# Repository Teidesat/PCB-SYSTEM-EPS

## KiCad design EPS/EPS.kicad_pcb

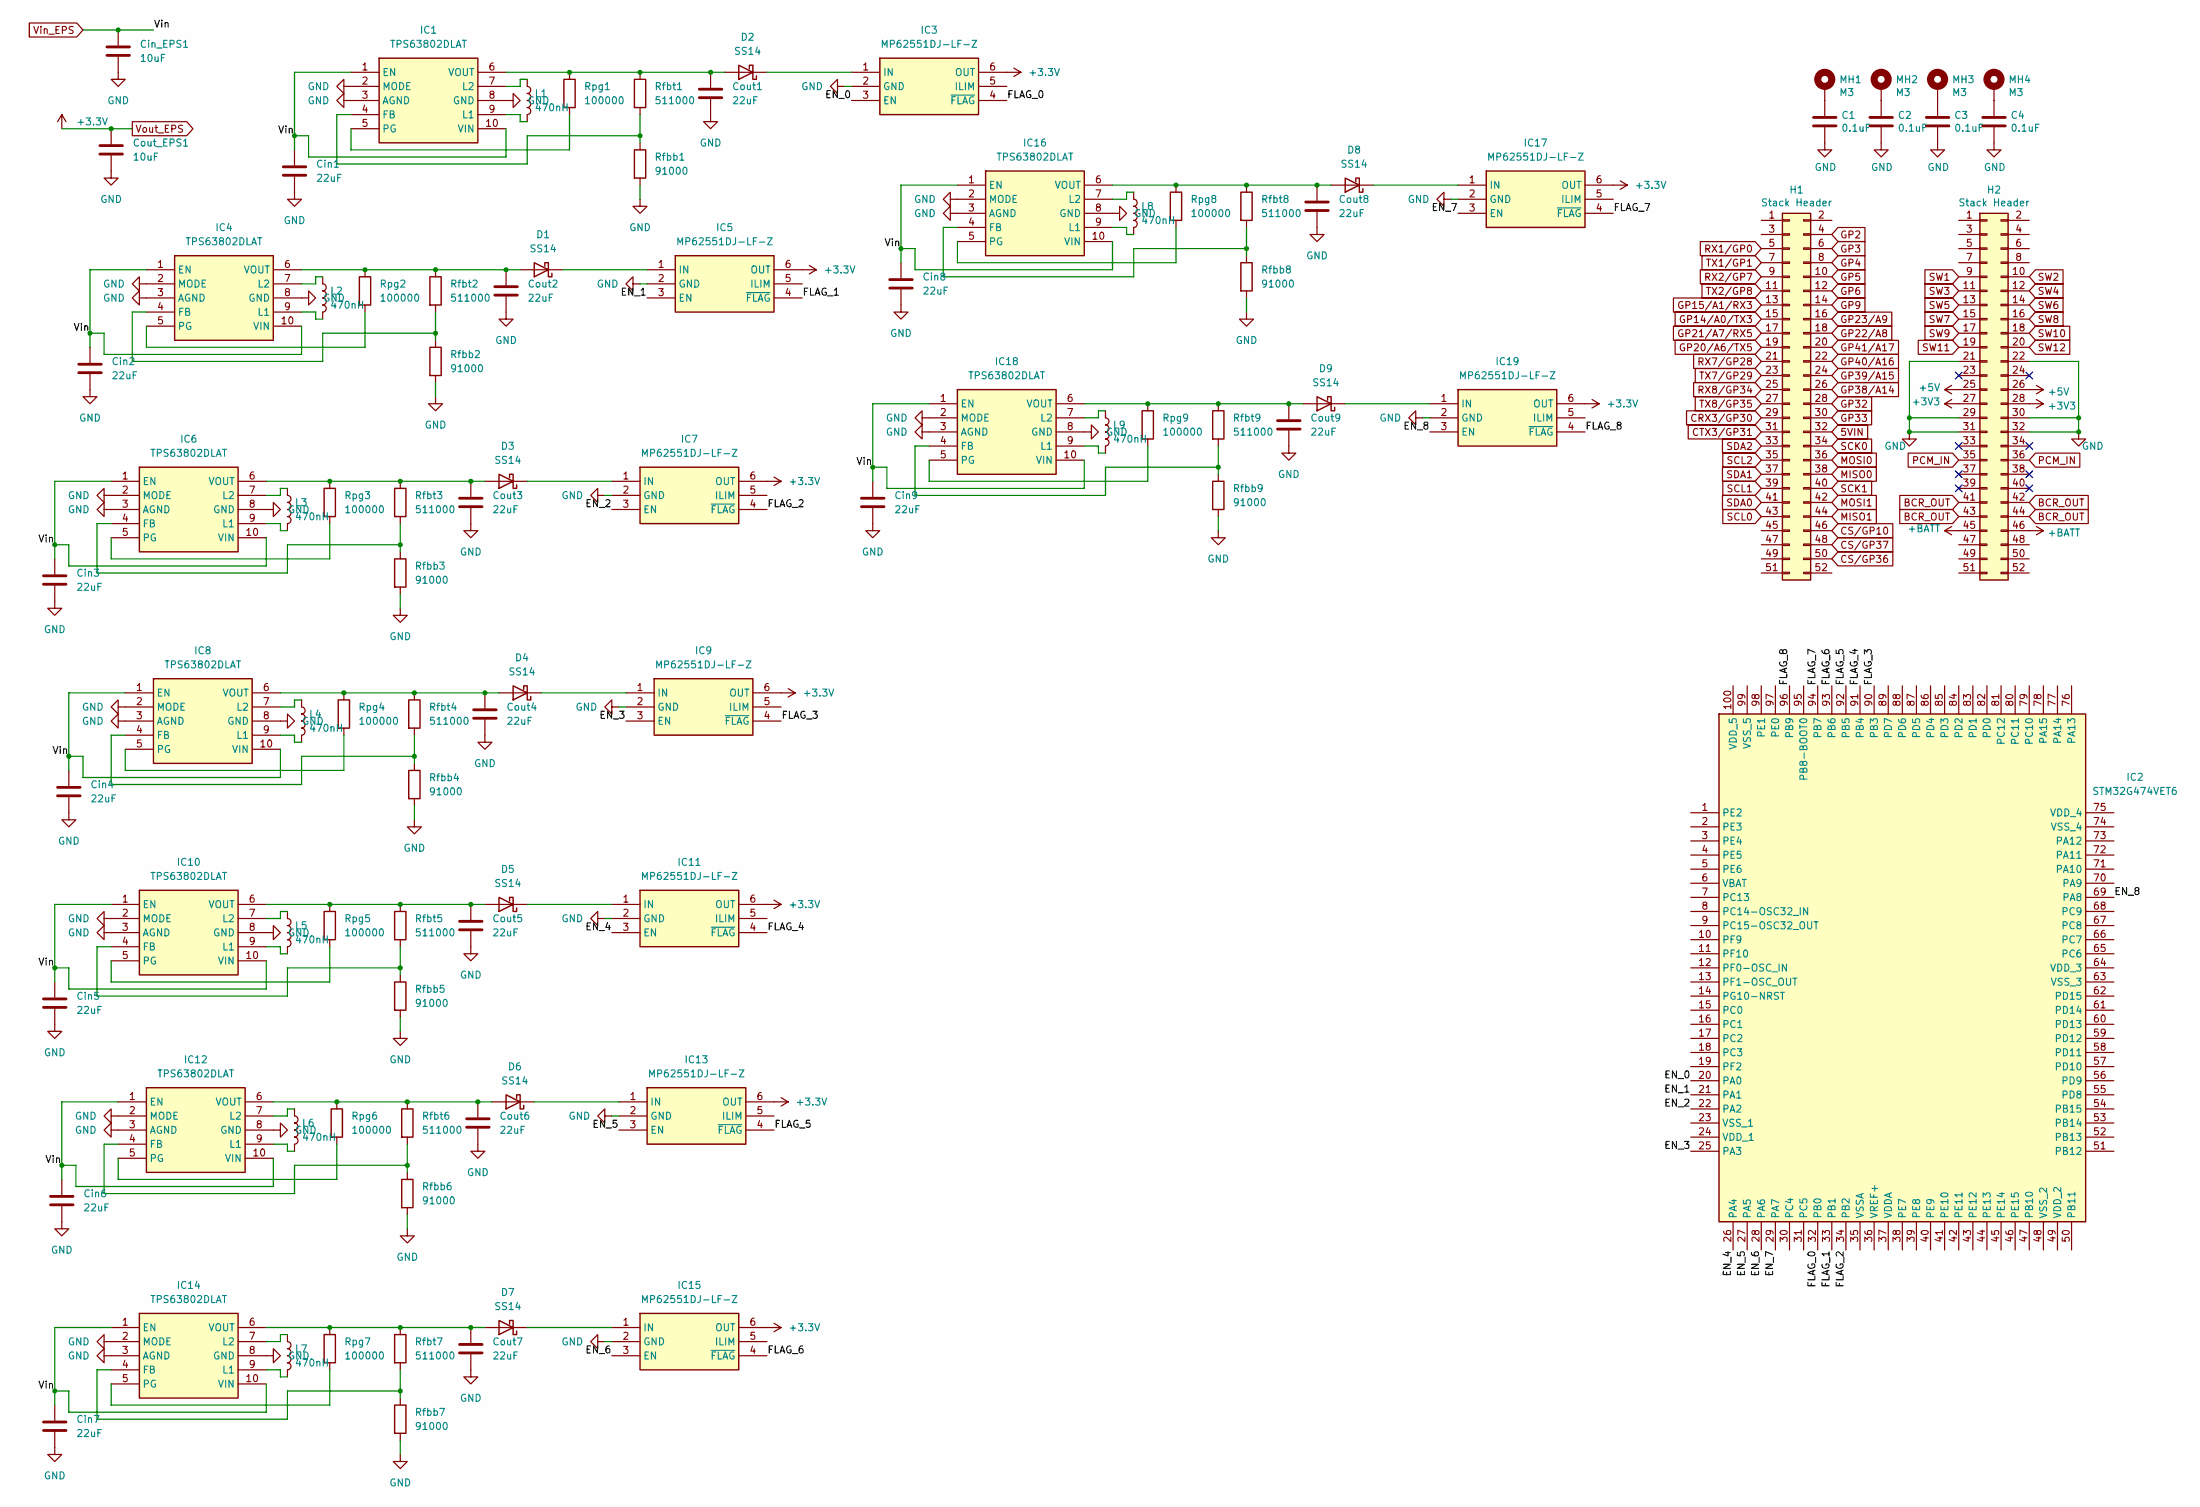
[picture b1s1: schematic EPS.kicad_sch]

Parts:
C1, C2, C3, C4: 0.1uF; C_0805_2012Metric
Cin1, Cin2, Cin3, Cin4, Cin5, Cin6, Cin7, Cin8, Cin9: 22uF; CP_Elec_6.3x4.5
Cin_EPS1: 10uF; C_0805_2012Metric
Cout1, Cout2, Cout3, Cout4, Cout5, Cout6, Cout7, Cout8, Cout9: 22uF; CP_Elec_6.3x4.5
Cout_EPS1: 10uF; C_0805_2012Metric
D1, D2, D3, D4, D5, D6, D7, D8, D9: SS14; D_SMA
H1, H2: Stack Header; PinHeader_2x26_P2.54mm_Vertical
IC1, IC4, IC6, IC8, IC10, IC12, IC14, IC16, IC18: TPS63802DLAT; Mouser Part Number 595-TPS63802DLAT
IC2: STM32G474VET6; QFP50P1600X1600X160-100N; Mouser Part Number 511-STM32G474VET6
IC3, IC5, IC7, IC9, IC11, IC13, IC15, IC17, IC19: MP62551DJ-LF-Z; SOT95P280X100-6N; Mouser Part Number 946-MP62551DJLFZ
L1, L2, L3, L4, L5, L6, L7, L8, L9: 470nH; L_1206_3216Metric_Pad1.42x1.75mm_HandSolder
MH1, MH2, MH3, MH4: M3; MountingHole_3.2mm_M3_Pad
Rfbb1, Rfbb2, Rfbb3, Rfbb4, Rfbb5, Rfbb6, Rfbb7, Rfbb8, Rfbb9: 91000; R_0603_1608Metric
Rfbt1, Rfbt2, Rfbt3, Rfbt4, Rfbt5, Rfbt6, Rfbt7, Rfbt8, Rfbt9: 511000; R_0603_1608Metric
Rpg1, Rpg2, Rpg3, Rpg4, Rpg5, Rpg6, Rpg7, Rpg8, Rpg9: 100000; R_0603_1608Metric

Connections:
5VIN: H1.32
+3V3: H2.27, H2.28
+5V: H2.25, H2.26
+BATT: H2.45, H2.46
/EN_0: IC2.20 (PA0), IC3.3 (EN)
/EN_1: IC2.21 (PA1), IC5.3 (EN)
/EN_2: IC2.22 (PA2), IC7.3 (EN)
/EN_3: IC2.25 (PA3), IC9.3 (EN)
/EN_4: IC2.26 (PA4), IC11.3 (EN)
/EN_5: IC2.27 (PA5), IC13.3 (EN)
/EN_6: IC2.28 (PA6), IC15.3 (EN)
/EN_7: IC2.29 (PA7), IC17.3 (EN)
/EN_8: IC2.69 (PA8), IC19.3 (EN)
/FLAG_0: IC2.32 (PB0), IC3.4 (~FLAG)
/FLAG_1: IC2.33 (PB1), IC5.4 (~FLAG)
/FLAG_2: IC2.34 (PB2), IC7.4 (~FLAG)
/FLAG_3: IC2.90 (PB3), IC9.4 (~FLAG)
/FLAG_4: IC2.91 (PB4), IC11.4 (~FLAG)
/FLAG_5: IC2.92 (PB5), IC13.4 (~FLAG)
/FLAG_6: IC2.93 (PB6), IC15.4 (~FLAG)
/FLAG_7: IC2.94 (PB7), IC17.4 (~FLAG)
/FLAG_8: IC2.96 (PB9), IC19.4 (~FLAG)
BCR_OUT: H2.41, H2.42, H2.43, H2.44
CRX3/GP30: H1.29
CS/GP10: H1.46
CS/GP36: H1.50
CS/GP37: H1.48
CTX3/GP31: H1.31
GND: C1.2, C2.2, C3.2, C4.2, Cin1.2, Cin2.2, Cin3.2, Cin4.2, Cin5.2, Cin6.2, Cin7.2, Cin8.2, Cin9.2, Cin_EPS1.2, Cout1.2, Cout2.2, Cout3.2, Cout4.2, Cout5.2, Cout6.2, Cout7.2, Cout8.2, Cout9.2, Cout_EPS1.2, H2.21, H2.22, H2.29, H2.30, H2.31, H2.32, IC1.2 (MODE), IC1.3 (AGND), IC1.8 (GND), IC3.2 (GND), IC4.2 (MODE), IC4.3 (AGND), IC4.8 (GND), IC5.2 (GND), IC6.2 (MODE), IC6.3 (AGND), IC6.8 (GND), IC7.2 (GND), IC8.2 (MODE), IC8.3 (AGND), IC8.8 (GND), IC9.2 (GND), IC10.2 (MODE), IC10.3 (AGND), IC10.8 (GND), IC11.2 (GND), IC12.2 (MODE), IC12.3 (AGND), IC12.8 (GND), IC13.2 (GND), IC14.2 (MODE), IC14.3 (AGND), IC14.8 (GND), IC15.2 (GND), IC16.2 (MODE), IC16.3 (AGND), IC16.8 (GND), IC17.2 (GND), IC18.2 (MODE), IC18.3 (AGND), IC18.8 (GND), IC19.2 (GND), Rfbb1.2, Rfbb2.2, Rfbb3.2, Rfbb4.2, Rfbb5.2, Rfbb6.2, Rfbb7.2, Rfbb8.2, Rfbb9.2
GP2: H1.4
GP3: H1.6
GP4: H1.8
GP5: H1.10
GP6: H1.12
GP9: H1.14
GP14/A0/TX3: H1.15
GP15/A1/RX3: H1.13
GP20/A6/TX5: H1.19
GP21/A7/RX5: H1.17
GP22/A8: H1.18
GP23/A9: H1.16
GP32: H1.28
GP33: H1.30
GP38/A14: H1.26
GP39/A15: H1.24
GP40/A16: H1.22
GP41/A17: H1.20
MISO0: H1.38
MISO1: H1.44
MOSI0: H1.36
MOSI1: H1.42
unnamed: C1.1, MH1.1
unnamed: C2.1, MH2.1
unnamed: C3.1, MH3.1
unnamed: C4.1, MH4.1
unnamed: Cout2.1, D1.2 (A), IC4.6 (VOUT), Rfbt2.1, Rpg2.1
unnamed: D1.1 (K), IC5.1 (IN)
unnamed: Cout1.1, D2.2 (A), IC1.6 (VOUT), Rfbt1.1, Rpg1.1
unnamed: D2.1 (K), IC3.1 (IN)
unnamed: Cout3.1, D3.2 (A), IC6.6 (VOUT), Rfbt3.1, Rpg3.1
unnamed: D3.1 (K), IC7.1 (IN)
unnamed: Cout4.1, D4.2 (A), IC8.6 (VOUT), Rfbt4.1, Rpg4.1
unnamed: D4.1 (K), IC9.1 (IN)
unnamed: Cout5.1, D5.2 (A), IC10.6 (VOUT), Rfbt5.1, Rpg5.1
unnamed: D5.1 (K), IC11.1 (IN)
unnamed: Cout6.1, D6.2 (A), IC12.6 (VOUT), Rfbt6.1, Rpg6.1
unnamed: D6.1 (K), IC13.1 (IN)
unnamed: Cout7.1, D7.2 (A), IC14.6 (VOUT), Rfbt7.1, Rpg7.1
unnamed: D7.1 (K), IC15.1 (IN)
unnamed: Cout8.1, D8.2 (A), IC16.6 (VOUT), Rfbt8.1, Rpg8.1
unnamed: D8.1 (K), IC17.1 (IN)
unnamed: Cout9.1, D9.2 (A), IC18.6 (VOUT), Rfbt9.1, Rpg9.1
unnamed: D9.1 (K), IC19.1 (IN)
unnamed: IC1.4 (FB), Rfbb1.1, Rfbt1.2
unnamed: IC1.9 (L1), L1.2
unnamed: IC1.7 (L2), L1.1
unnamed: IC1.5 (PG), Rpg1.2
unnamed: IC4.4 (FB), Rfbb2.1, Rfbt2.2
unnamed: IC4.9 (L1), L2.2
unnamed: IC4.7 (L2), L2.1
unnamed: IC4.5 (PG), Rpg2.2
unnamed: IC6.4 (FB), Rfbb3.1, Rfbt3.2
unnamed: IC6.9 (L1), L3.2
unnamed: IC6.7 (L2), L3.1
unnamed: IC6.5 (PG), Rpg3.2
unnamed: IC8.4 (FB), Rfbb4.1, Rfbt4.2
unnamed: IC8.9 (L1), L4.2
unnamed: IC8.7 (L2), L4.1
unnamed: IC8.5 (PG), Rpg4.2
unnamed: IC10.4 (FB), Rfbb5.1, Rfbt5.2
unnamed: IC10.9 (L1), L5.2
unnamed: IC10.7 (L2), L5.1
unnamed: IC10.5 (PG), Rpg5.2
unnamed: IC12.4 (FB), Rfbb6.1, Rfbt6.2
unnamed: IC12.9 (L1), L6.2
unnamed: IC12.7 (L2), L6.1
unnamed: IC12.5 (PG), Rpg6.2
unnamed: IC14.4 (FB), Rfbb7.1, Rfbt7.2
unnamed: IC14.9 (L1), L7.2
unnamed: IC14.7 (L2), L7.1
unnamed: IC14.5 (PG), Rpg7.2
unnamed: IC16.4 (FB), Rfbb8.1, Rfbt8.2
unnamed: IC16.9 (L1), L8.2
unnamed: IC16.7 (L2), L8.1
unnamed: IC16.5 (PG), Rpg8.2
unnamed: IC18.4 (FB), Rfbb9.1, Rfbt9.2
unnamed: IC18.9 (L1), L9.2
unnamed: IC18.7 (L2), L9.1
unnamed: IC18.5 (PG), Rpg9.2
PCM_IN: H2.35, H2.36
RX1/GP0: H1.5
RX2/GP7: H1.9
RX7/GP28: H1.21
RX8/GP34: H1.25
SCK0: H1.34
SCK1: H1.40
SCL0: H1.43
SCL1: H1.39
SCL2: H1.35
SDA0: H1.41
SDA1: H1.37
SDA2: H1.33
SW1: H2.9
SW2: H2.10
SW3: H2.11
SW4: H2.12
SW5: H2.13
SW6: H2.14
SW7: H2.15
SW8: H2.16
SW9: H2.17
SW10: H2.18
SW11: H2.19
SW12: H2.20
TX1/GP1: H1.7
TX2/GP8: H1.11
TX7/GP29: H1.23
TX8/GP35: H1.27
Vin_EPS: Cin1.1, Cin2.1, Cin3.1, Cin4.1, Cin5.1, Cin6.1, Cin7.1, Cin8.1, Cin9.1, Cin_EPS1.1, IC1.1 (EN), IC1.10 (VIN), IC4.1 (EN), IC4.10 (VIN), IC6.1 (EN), IC6.10 (VIN), IC8.1 (EN), IC8.10 (VIN), IC10.1 (EN), IC10.10 (VIN), IC12.1 (EN), IC12.10 (VIN), IC14.1 (EN), IC14.10 (VIN), IC16.1 (EN), IC16.10 (VIN), IC18.1 (EN), IC18.10 (VIN)
Vout_EPS: Cout_EPS1.1, IC3.6 (OUT), IC5.6 (OUT), IC7.6 (OUT), IC9.6 (OUT), IC11.6 (OUT), IC13.6 (OUT), IC15.6 (OUT), IC17.6 (OUT), IC19.6 (OUT)

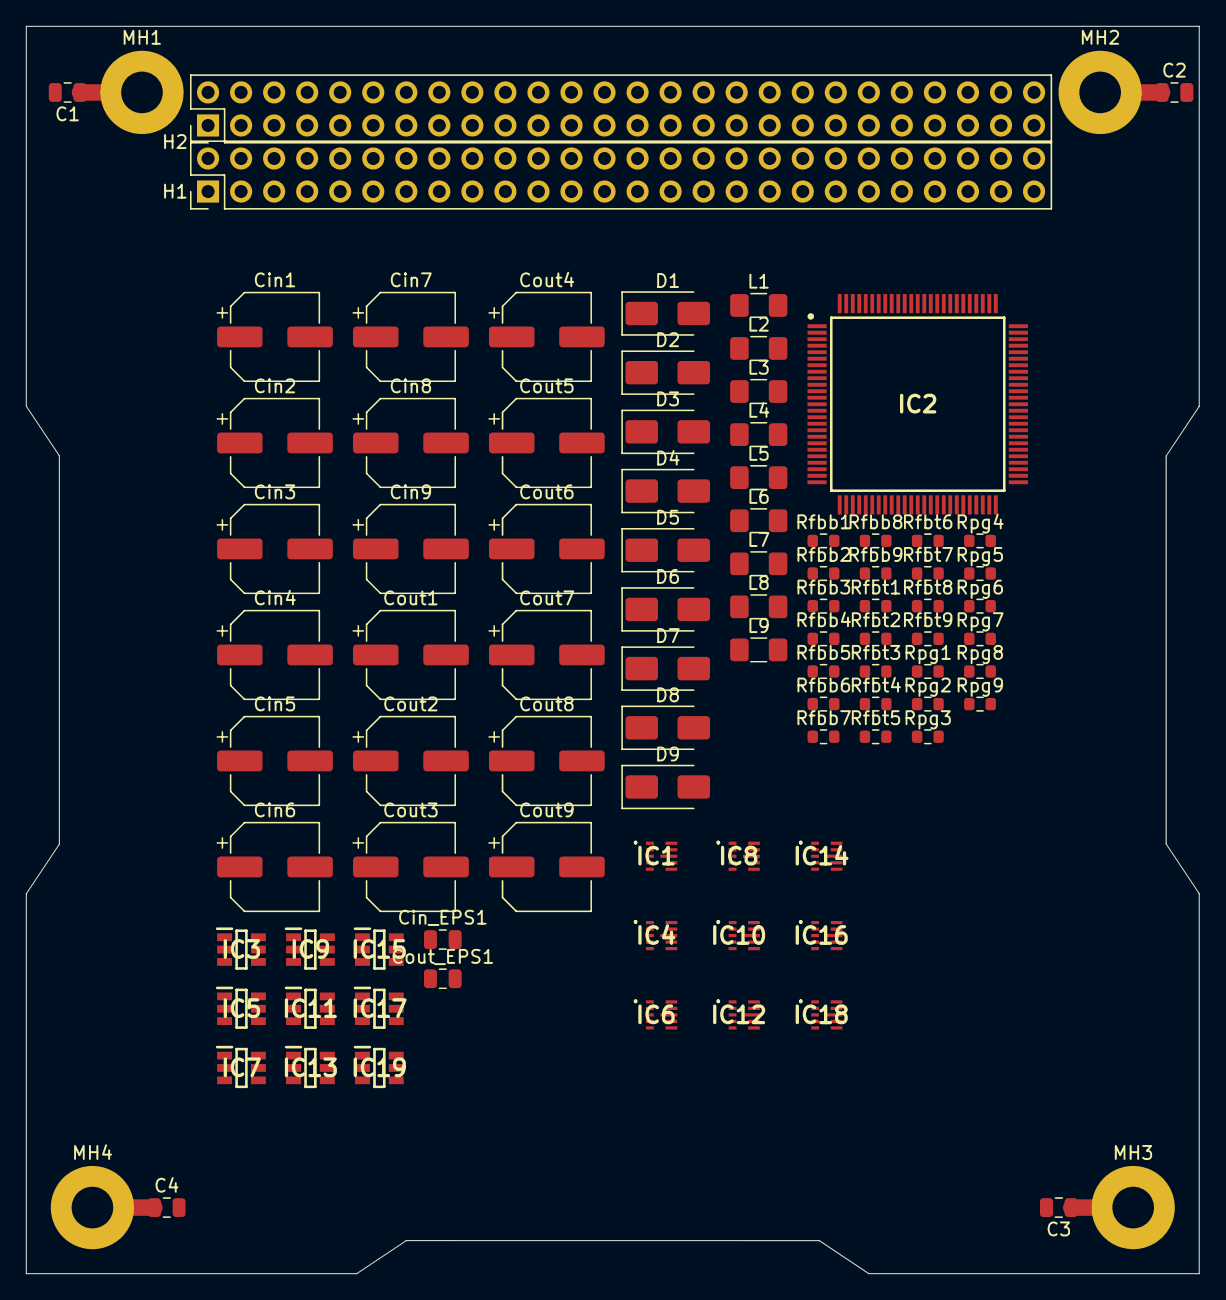
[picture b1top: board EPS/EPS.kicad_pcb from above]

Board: 2 copper layers, 90.2 x 95.9 mm, 94 parts (0 on the bottom side), 84 nets.

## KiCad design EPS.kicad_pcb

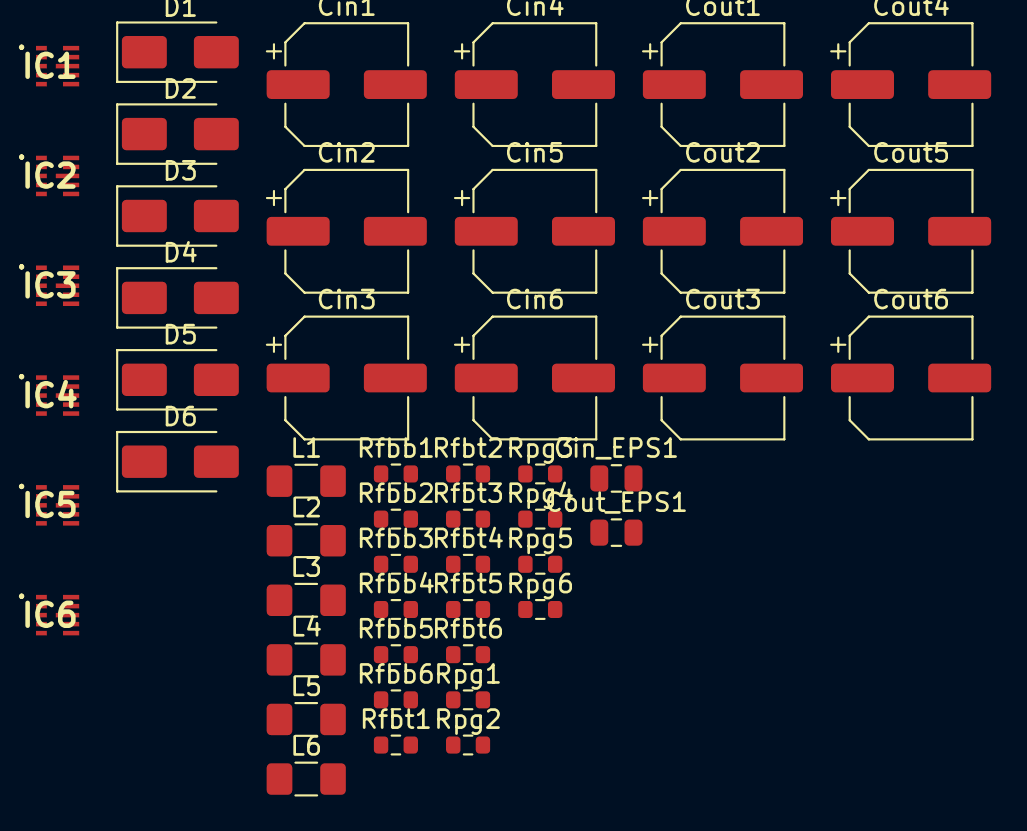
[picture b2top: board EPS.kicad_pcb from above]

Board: 2 copper layers, 50 parts (0 on the bottom side), 33 nets, no tracks yet.

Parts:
Cin1, Cin2, Cin3, Cin4, Cin5, Cin6: 22uF; CP_Elec_6.3x4.5
Cin_EPS1: 10uF; C_0805_2012Metric
Cout1, Cout2, Cout3, Cout4, Cout5, Cout6: 22uF; CP_Elec_6.3x4.5
Cout_EPS1: 10uF; C_0805_2012Metric
D1, D2, D3, D4, D5, D6: SS14; D_SMA
IC1, IC2, IC3, IC4, IC5, IC6: TPS63802DLAT
L1, L2, L3, L4, L5, L6: 470nH; L_1206_3216Metric_Pad1.42x1.75mm_HandSolder
Rfbb1, Rfbb2, Rfbb3, Rfbb4, Rfbb5, Rfbb6: 91000; R_0603_1608Metric
Rfbt1, Rfbt2, Rfbt3, Rfbt4, Rfbt5, Rfbt6: 511000; R_0603_1608Metric
Rpg1, Rpg2, Rpg3, Rpg4, Rpg5, Rpg6: 100000; R_0603_1608Metric

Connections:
GND: Cin1.2, Cin2.2, Cin3.2, Cin4.2, Cin5.2, Cin6.2, Cin_EPS1.2, Cout1.2, Cout2.2, Cout3.2, Cout4.2, Cout5.2, Cout6.2, Cout_EPS1.2, IC1.2 (MODE), IC1.3 (AGND), IC1.8 (GND), IC2.2 (MODE), IC2.3 (AGND), IC2.8 (GND), IC3.2 (MODE), IC3.3 (AGND), IC3.8 (GND), IC4.2 (MODE), IC4.3 (AGND), IC4.8 (GND), IC5.2 (MODE), IC5.3 (AGND), IC5.8 (GND), IC6.2 (MODE), IC6.3 (AGND), IC6.8 (GND), Rfbb1.2, Rfbb2.2, Rfbb3.2, Rfbb4.2, Rfbb5.2, Rfbb6.2
unnamed: Cout5.1, D1.2 (A), IC5.6 (VOUT), Rfbt5.1, Rpg5.1
unnamed: Cout1.1, D2.2 (A), IC1.6 (VOUT), Rfbt1.1, Rpg1.1
unnamed: Cout2.1, D3.2 (A), IC2.6 (VOUT), Rfbt2.1, Rpg2.1
unnamed: Cout3.1, D4.2 (A), IC3.6 (VOUT), Rfbt3.1, Rpg3.1
unnamed: Cout4.1, D5.2 (A), IC4.6 (VOUT), Rfbt4.1, Rpg4.1
unnamed: Cout6.1, D6.2 (A), IC6.6 (VOUT), Rfbt6.1, Rpg6.1
unnamed: IC1.4 (FB), Rfbb1.1, Rfbt1.2
unnamed: IC1.9 (L1), L1.2
unnamed: IC1.7 (L2), L1.1
unnamed: IC1.5 (PG), Rpg1.2
unnamed: IC2.4 (FB), Rfbb2.1, Rfbt2.2
unnamed: IC2.9 (L1), L2.2
unnamed: IC2.7 (L2), L2.1
unnamed: IC2.5 (PG), Rpg2.2
unnamed: IC3.4 (FB), Rfbb3.1, Rfbt3.2
unnamed: IC3.9 (L1), L3.2
unnamed: IC3.7 (L2), L3.1
unnamed: IC3.5 (PG), Rpg3.2
unnamed: IC4.4 (FB), Rfbb4.1, Rfbt4.2
unnamed: IC4.9 (L1), L4.2
unnamed: IC4.7 (L2), L4.1
unnamed: IC4.5 (PG), Rpg4.2
unnamed: IC5.4 (FB), Rfbb5.1, Rfbt5.2
unnamed: IC5.9 (L1), L5.2
unnamed: IC5.7 (L2), L5.1
unnamed: IC5.5 (PG), Rpg5.2
unnamed: IC6.4 (FB), Rfbb6.1, Rfbt6.2
unnamed: IC6.9 (L1), L6.2
unnamed: IC6.7 (L2), L6.1
unnamed: IC6.5 (PG), Rpg6.2
Vin_EPS: Cin1.1, Cin2.1, Cin3.1, Cin4.1, Cin5.1, Cin6.1, Cin_EPS1.1, IC1.1 (EN), IC1.10 (VIN), IC2.1 (EN), IC2.10 (VIN), IC3.1 (EN), IC3.10 (VIN), IC4.1 (EN), IC4.10 (VIN), IC5.1 (EN), IC5.10 (VIN), IC6.1 (EN), IC6.10 (VIN)
Vout_EPS: Cout_EPS1.1, D1.1 (K), D2.1 (K), D3.1 (K), D4.1 (K), D5.1 (K), D6.1 (K)

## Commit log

2025-11-19 ignore para eliminar archivos no deseados
    Removed and added various patterns to the .gitignore file to better manage temporary and backup files.
2025-11-19 Mover EPS.kicad_pcb a la carpeta EPS
2025-12-01 Add files via upload
    Al sistema EPS se le añadió el micro, y el componente encargado de la proteccion, hay que modificar las uniones todavia, y a ser posible añadir sensores para medir lo que nos interesa
